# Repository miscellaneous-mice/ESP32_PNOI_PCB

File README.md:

# ESP32_PNOI_PCB

This is a ESP32 Footprint PCB design that contains ESP32, 4-Pin RGB LED pin connector with its resistor, 2 MEMS microphone, SD card slot

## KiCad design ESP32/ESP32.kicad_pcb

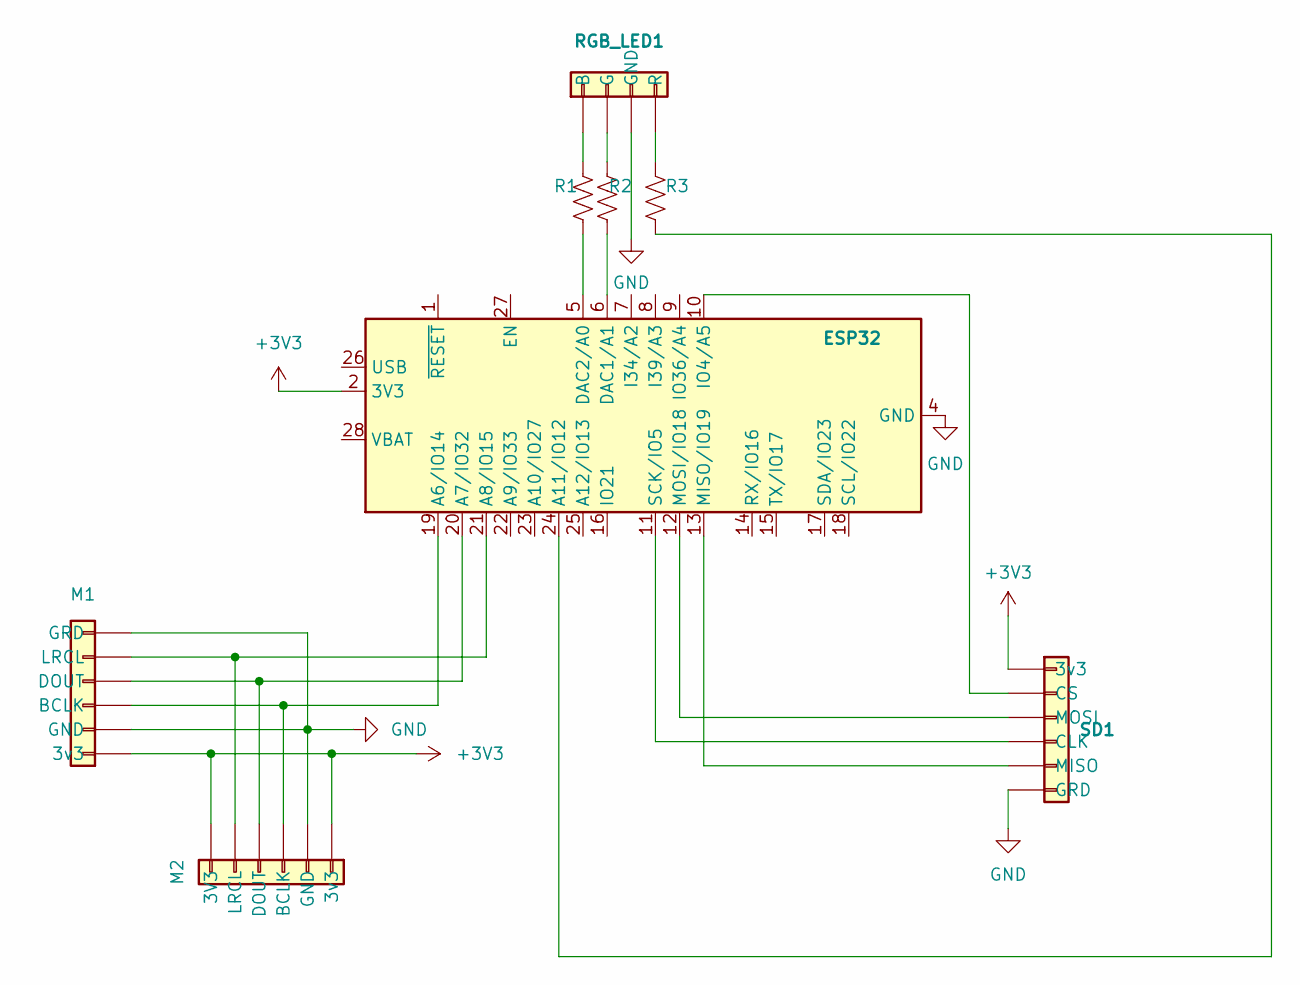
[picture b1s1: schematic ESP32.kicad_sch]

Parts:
ESP32: Adafruit_Feather_HUZZAH32_ESP32; Adafruit_Feather
M1, M2: Conn_01x06; PinHeader_1x06_P2.54mm_Vertical
R1, R2, R3: R_US; R_Box_L8.4mm_W2.5mm_P5.08mm
RGB_LED1: Conn_01x04; PinHeader_1x04_P2.54mm_Vertical
SD1: Conn_01x06; PinHeader_1x06_P2.54mm_Vertical

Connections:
+3V3: ESP32.2 (3V3), M1.1 (3v3), M2.1 (3v3), M2.6 (3V3), SD1.1 (3v3)
GND: ESP32.4 (GND), M1.2 (GND), M1.6 (GRD), M2.2 (GND), RGB_LED1.3 (GND), SD1.6 (GRD)
unnamed: ESP32.5 (DAC2/A0), R1.2
unnamed: ESP32.6 (DAC1/A1), R2.2
unnamed: ESP32.10 (IO4/A5), SD1.2 (CS)
unnamed: ESP32.11 (SCK/IO5), SD1.4 (CLK)
unnamed: ESP32.12 (MOSI/IO18), SD1.3 (MOSI)
unnamed: ESP32.13 (MISO/IO19), SD1.5 (MISO)
unnamed: ESP32.19 (A6/IO14), M1.3 (BCLK), M2.3 (BCLK)
unnamed: ESP32.20 (A7/IO32), M1.4 (DOUT), M2.4 (DOUT)
unnamed: ESP32.21 (A8/IO15), M1.5 (LRCL), M2.5 (LRCL)
unnamed: ESP32.24 (A11/IO12), R3.2
unnamed: R1.1, RGB_LED1.1 (B)
unnamed: R2.1, RGB_LED1.2 (G)
unnamed: R3.1, RGB_LED1.4 (R)

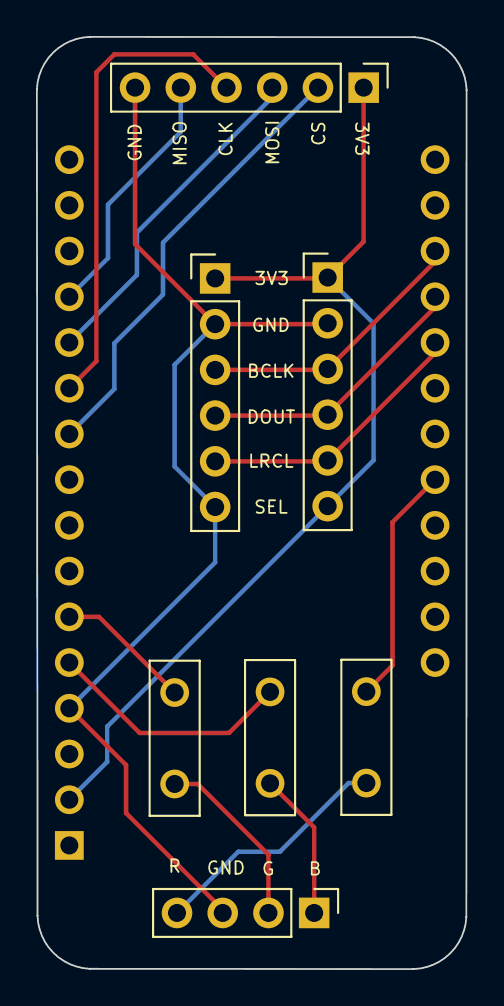
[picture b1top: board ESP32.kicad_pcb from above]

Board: 2 copper layers, 23.9 x 51.8 mm, 8 parts (1 on the bottom side), 15 nets.
